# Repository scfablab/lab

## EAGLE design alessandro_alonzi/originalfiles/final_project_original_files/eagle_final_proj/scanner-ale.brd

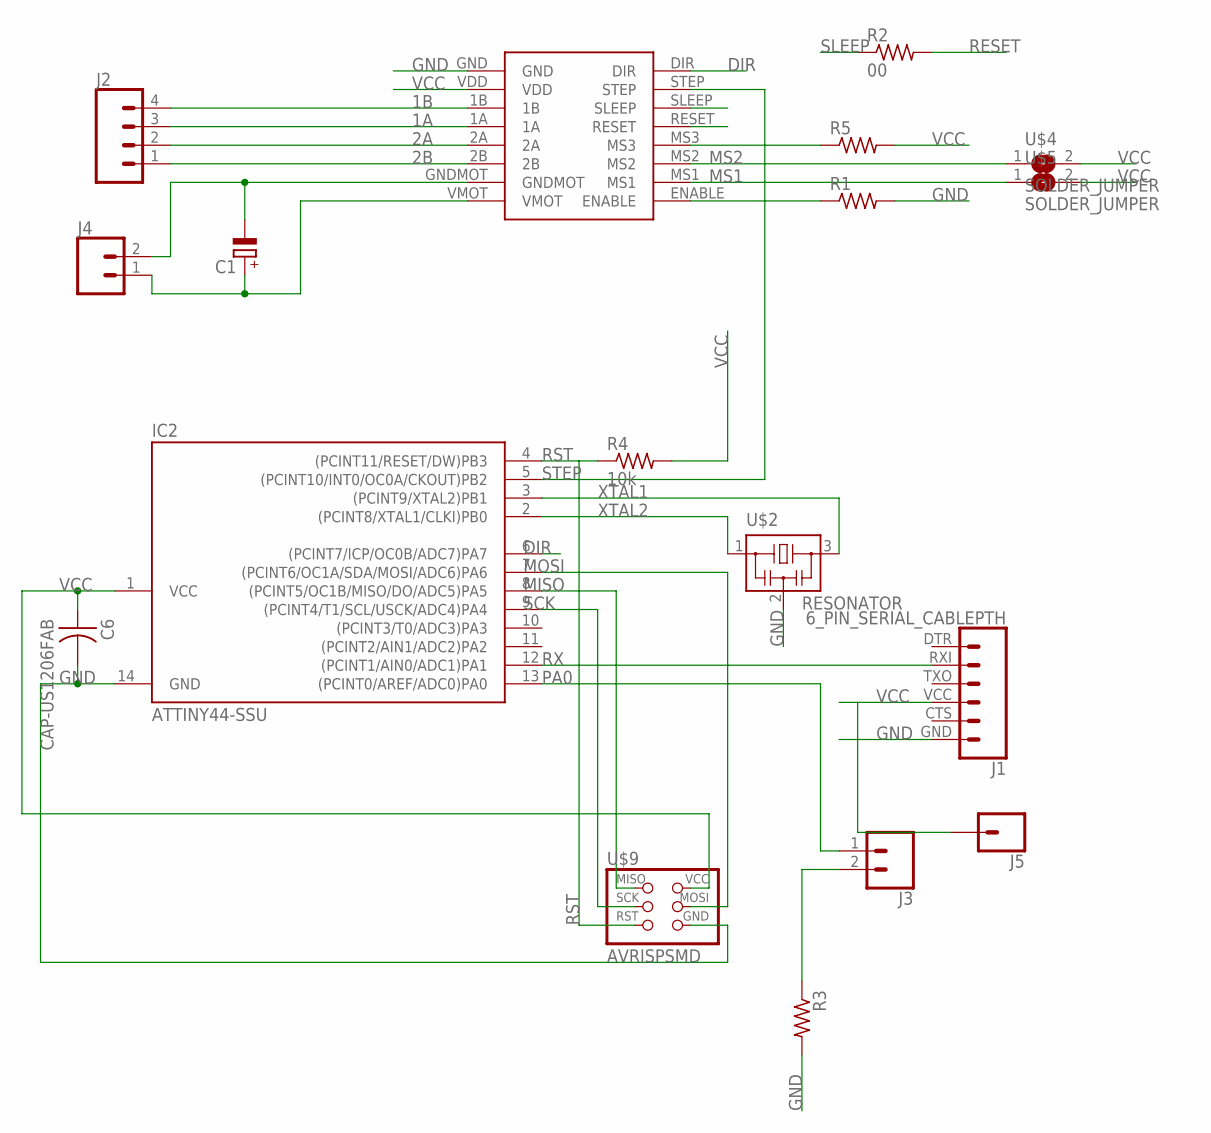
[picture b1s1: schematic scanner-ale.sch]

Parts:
C1: CPOL-EUE2,5-6E; E2,5-6E
C6: CAP-US1206FAB; C1206FAB
IC2: ATTINY44-SSU; SOIC14
J1: 6_PIN_SERIAL_CABLEPTH; FTDI_BASIC
J2: CONN_04; 1X04
J3, J4: CONN_02; 1X02
J5: CONN_01; 1X01
R1, R3, R5: RES-US1206FAB; R1206FAB
R2: 00; R1206FAB
R4: 10k; R1206FAB
U$1: POLOLUESTEPPERDRIVERDIL16MAT; DIL16
U$2: RESONATOR; EFOBM
U$4, U$5: SOLDER_JUMPER; SJFAB
U$9: AVRISPSMD; 2X03SMD

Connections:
1A: J2.3, U$1.1A
1B: J2.4, U$1.1B
2A: J2.2, U$1.2A
2B: J2.1, U$1.2B
DIR: IC2.6 ((PCINT7/ICP/OC0B/ADC7)PA7), U$1.DIR
GND: C6.2, IC2.14 (GND), J1.GND (6), R1.2, R3.2, U$1.GND, U$2.2, U$9.6 (GND)
MISO: IC2.8 ((PCINT5/OC1B/MISO/DO/ADC5)PA5), U$9.1 (MISO)
MOSI: IC2.7 ((PCINT6/OC1A/SDA/MOSI/ADC6)PA6), U$9.4 (MOSI)
MS1: U$1.MS1, U$5.1
MS2: U$1.MS2, U$4.1
unnamed: C1.-, J4.2, U$1.GNDMOT
unnamed: R1.1, U$1.ENABLE
unnamed: C1.+, J4.1, U$1.VMOT
unnamed: J3.2, R3.1
unnamed: R5.1, U$1.MS3
PA0: IC2.13 ((PCINT0/AREF/ADC0)PA0), J3.1
RESET: R2.2, U$1.RESET
RST: IC2.4 ((PCINT11/RESET/DW)PB3), R4.1, U$9.5 (RST)
RX: IC2.12 ((PCINT1/AIN0/ADC1)PA1), J1.RXI (2)
SCK: IC2.9 ((PCINT4/T1/SCL/USCK/ADC4)PA4), U$9.3 (SCK)
SLEEP: R2.1, U$1.SLEEP
STEP: IC2.5 ((PCINT10/INT0/OC0A/CKOUT)PB2), U$1.STEP
VCC: C6.1, IC2.1 (VCC), J1.VCC (4), J5.1, R4.2, R5.2, U$1.VDD, U$4.2, U$5.2, U$9.2 (VCC)
XTAL1: IC2.3 ((PCINT9/XTAL2)PB1), U$2.3
XTAL2: IC2.2 ((PCINT8/XTAL1/CLKI)PB0), U$2.1

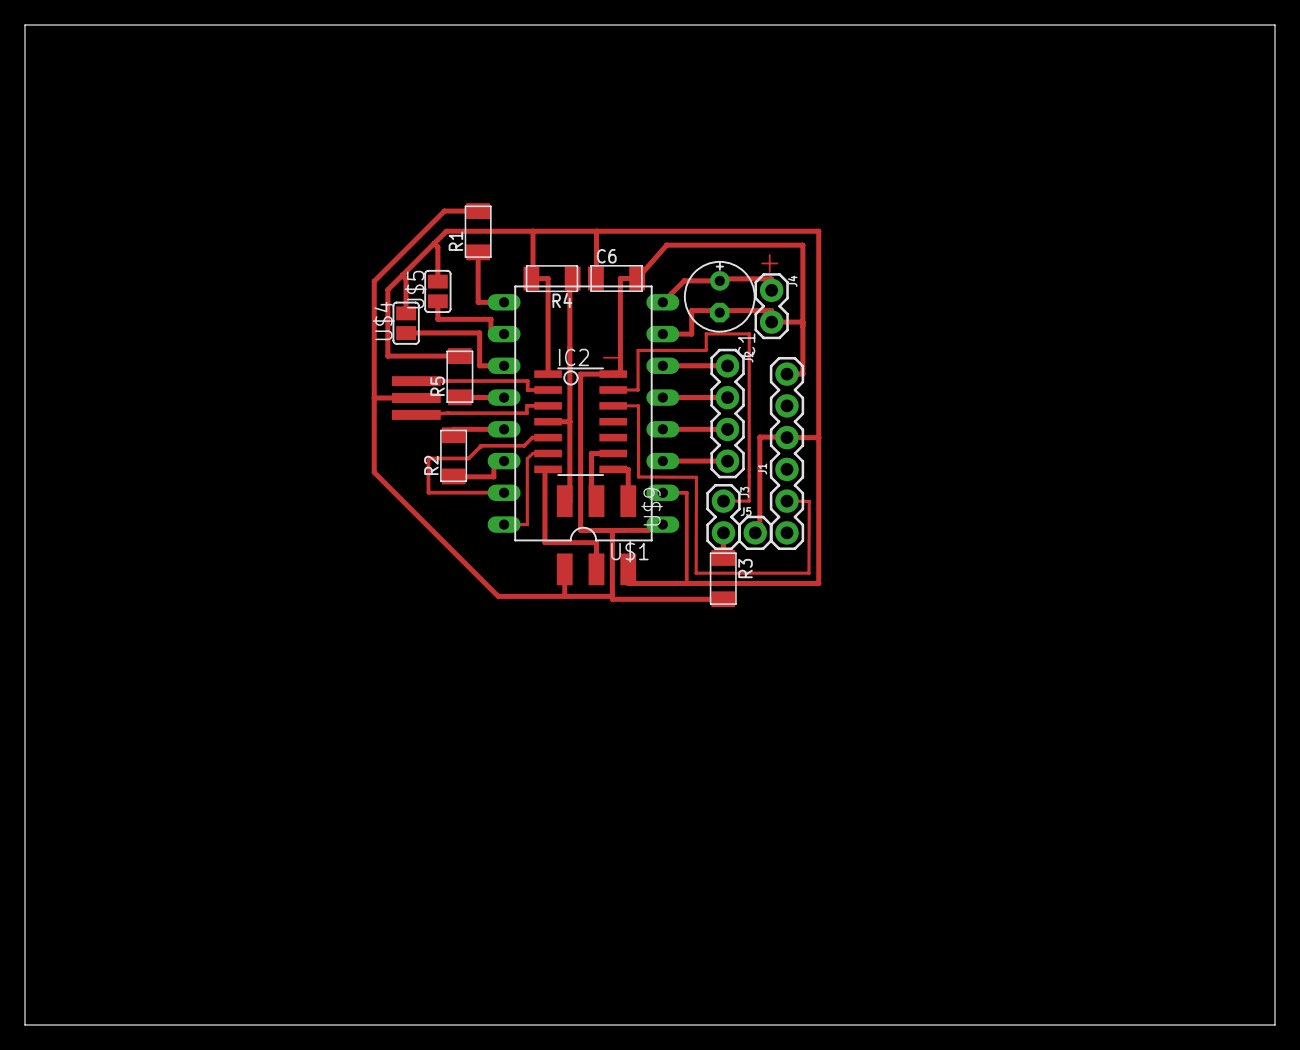
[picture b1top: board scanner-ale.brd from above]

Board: 2 copper layers, 100.0 x 80.0 mm, 18 parts (0 on the bottom side), 25 nets.

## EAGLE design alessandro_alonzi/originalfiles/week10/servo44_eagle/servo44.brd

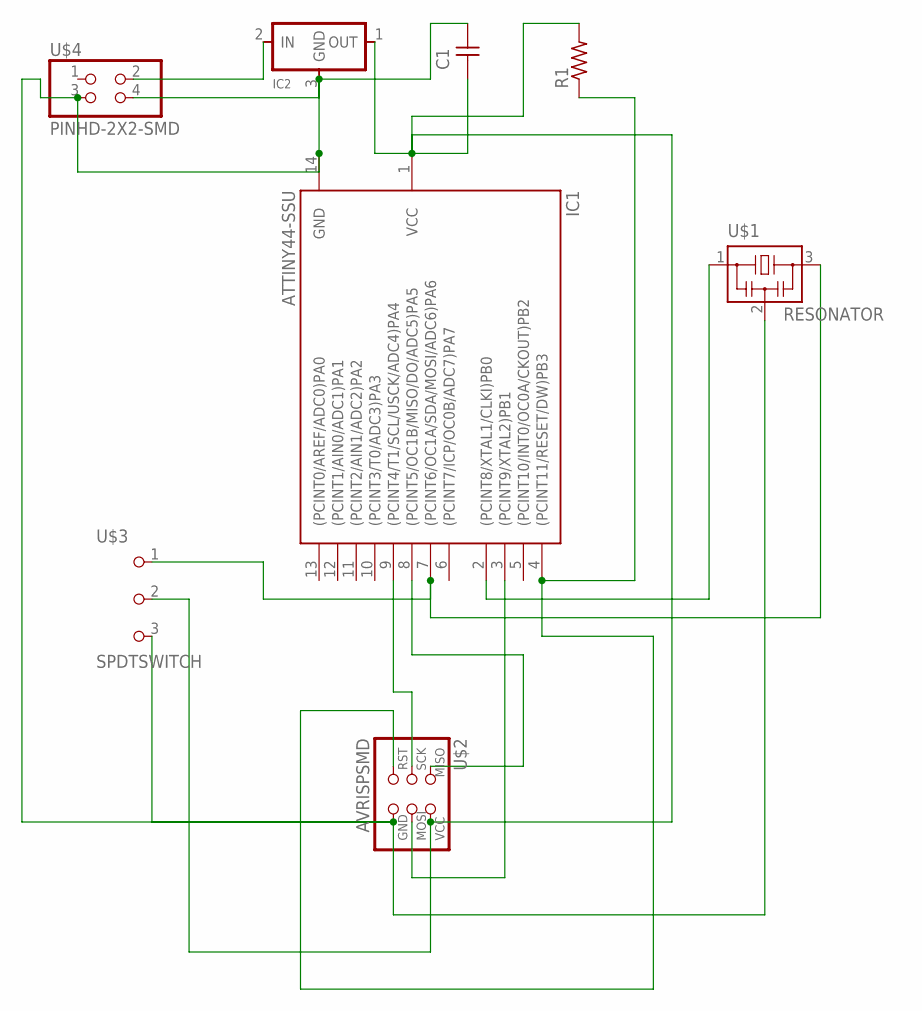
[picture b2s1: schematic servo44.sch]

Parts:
C1: CAP-UNPOLARIZEDFAB; C1206FAB
IC1: ATTINY44-SSU; SOIC14
IC2: REGULATORSOT23; SOT23
R1: RES-US1206FAB; R1206FAB
U$1: RESONATOR; EFOBM
U$2: AVRISPSMD; 2X03SMD
U$3: SPDTSWITCH
U$4: PINHD-2X2-SMD; 2X02SMD

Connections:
unnamed: IC1.8 ((PCINT5/OC1B/MISO/DO/ADC5)PA5), U$2.1 (MISO)
unnamed: IC1.9 ((PCINT4/T1/SCL/USCK/ADC4)PA4), U$2.3 (SCK)
unnamed: IC1.4 ((PCINT11/RESET/DW)PB3), R1.1, U$2.5 (RST)
unnamed: IC2.2 (IN), U$4.2
unnamed: IC1.7 ((PCINT6/OC1A/SDA/MOSI/ADC6)PA6), U$2.4 (MOSI), U$3.1
unnamed: C1.2, IC1.14 (GND), IC2.3 (GND), U$1.2, U$2.6 (GND), U$3.3, U$4.3, U$4.4
unnamed: IC1.2 ((PCINT8/XTAL1/CLKI)PB0), U$1.1
unnamed: IC1.3 ((PCINT9/XTAL2)PB1), U$1.3
unnamed: C1.1, IC1.1 (VCC), IC2.1 (OUT), R1.2, U$2.2 (VCC), U$3.2

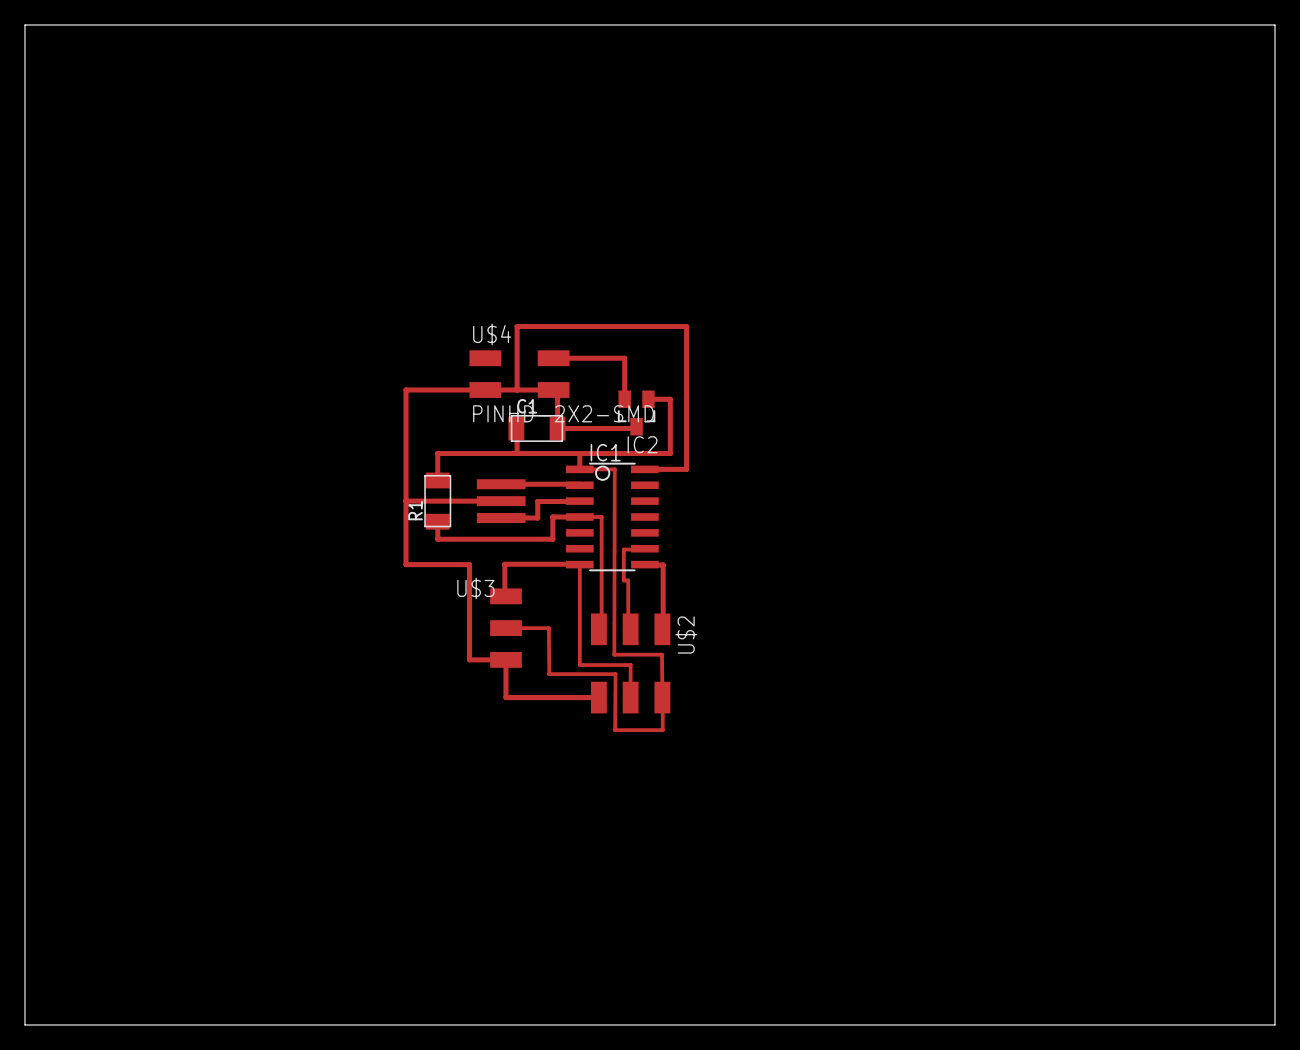
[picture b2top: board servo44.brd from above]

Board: 2 copper layers, 100.0 x 80.0 mm, 8 parts (0 on the bottom side), 9 nets.

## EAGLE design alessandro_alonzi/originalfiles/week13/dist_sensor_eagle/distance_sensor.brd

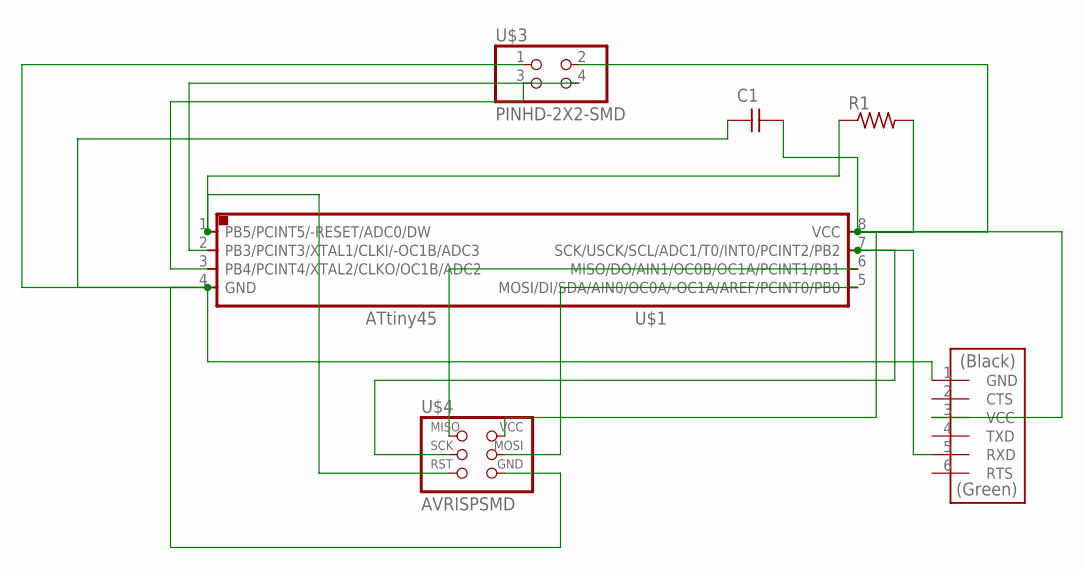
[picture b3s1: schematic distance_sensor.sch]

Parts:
C1: CAP-UNPOLARIZEDFAB; C1206FAB
R1: RES-US1206FAB; R1206FAB
U$1: ATTINY45SI; SOIC8
U$2: FTDI-SMD-HEADER; 1X06SMD
U$3: PINHD-2X2-SMD; 2X02SMD
U$4: AVRISPSMD; 2X03SMD

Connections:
unnamed: C1.1, U$1.4 (GND), U$2.1 (GND), U$3.1, U$4.6 (GND)
unnamed: C1.2, R1.2, U$1.8 (VCC), U$2.3 (VCC), U$3.2, U$4.2 (VCC)
unnamed: U$1.7 (SCK/USCK/SCL/ADC1/T0/INT0/PCINT2/PB2), U$2.5 (RXD), U$4.3 (SCK)
unnamed: U$1.3 (PB4/PCINT4/XTAL2/CLKO/OC1B/ADC2), U$3.3
unnamed: U$1.2 (PB3/PCINT3/XTAL1/CLKI/-OC1B/ADC3), U$3.4
unnamed: U$1.6 (MISO/DO/AIN1/OC0B/OC1A/PCINT1/PB1), U$4.1 (MISO)
unnamed: U$1.5 (MOSI/DI/SDA/AIN0/OC0A/-OC1A/AREF/PCINT0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), U$4.4 (MOSI)
unnamed: R1.1, U$1.1 (PB5/PCINT5/-RESET/ADC0/DW), U$4.5 (RST)

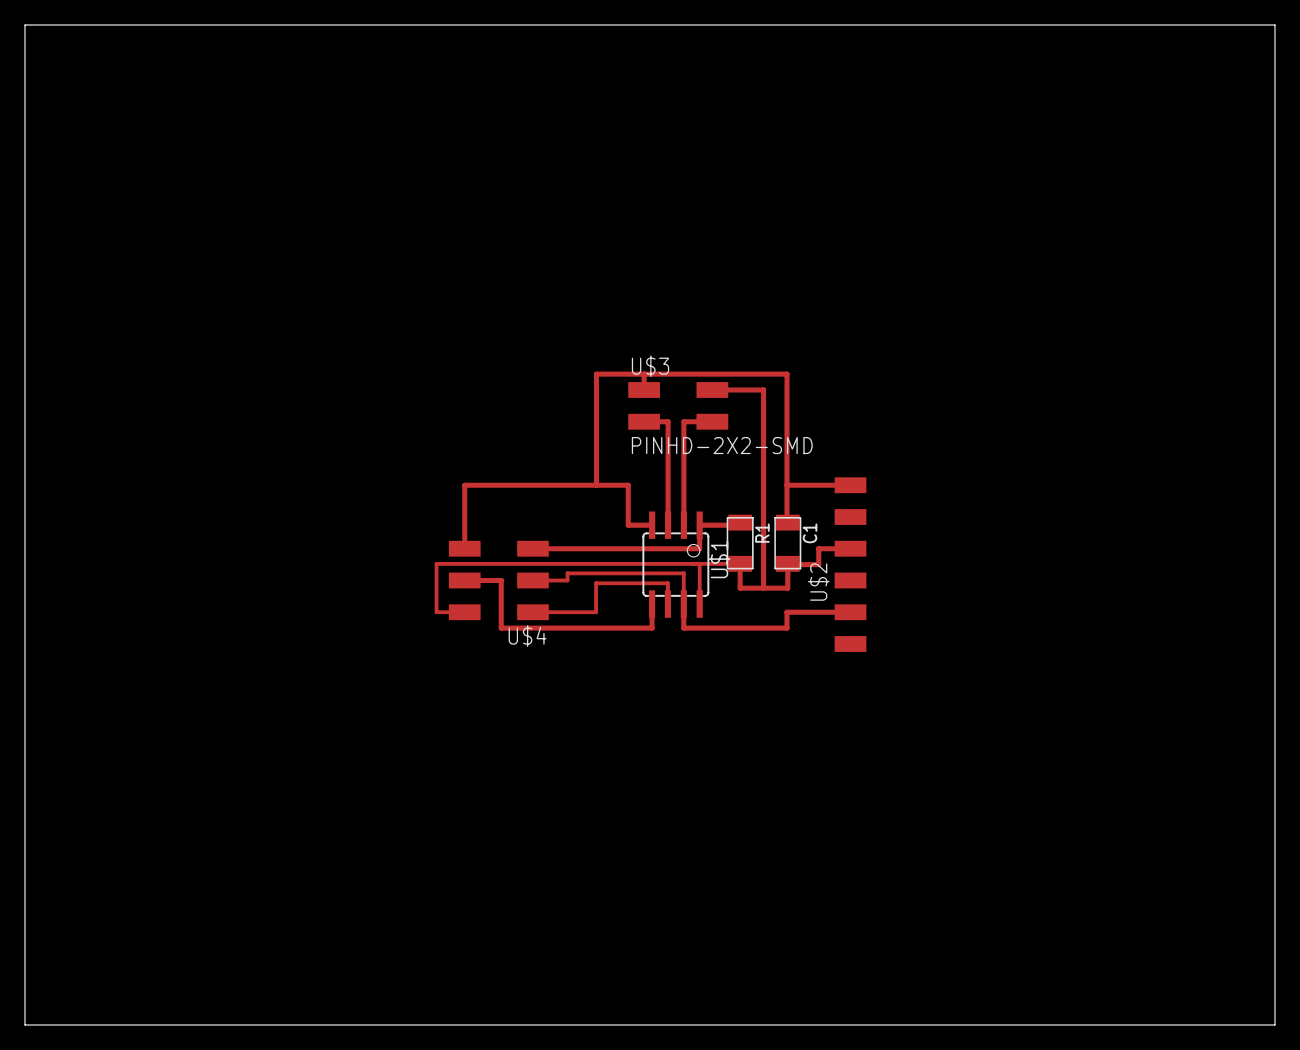
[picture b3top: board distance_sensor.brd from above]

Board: 2 copper layers, 100.0 x 80.0 mm, 6 parts (0 on the bottom side), 8 nets.

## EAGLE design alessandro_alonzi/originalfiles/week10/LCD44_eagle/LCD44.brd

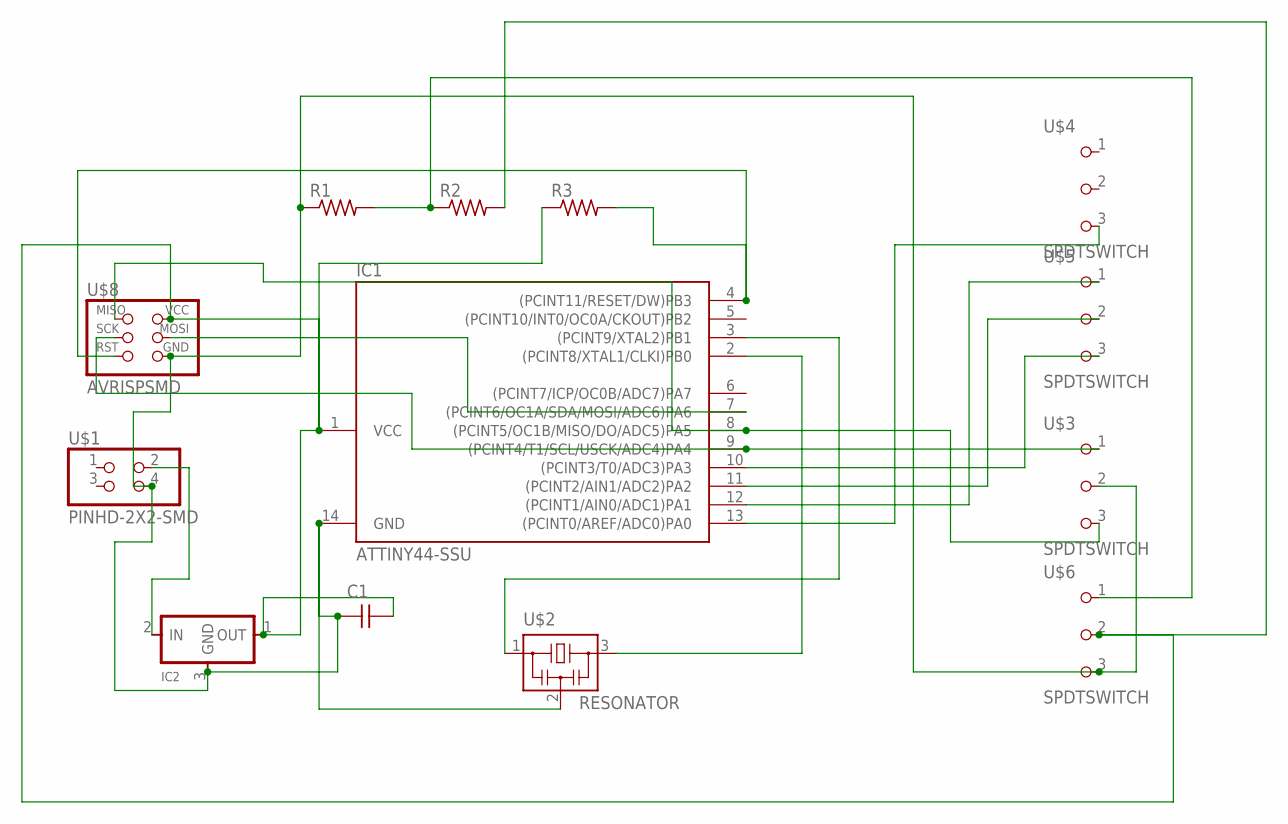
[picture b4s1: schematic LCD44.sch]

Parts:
C1: CAP-UNPOLARIZEDFAB; C1206FAB
IC1: ATTINY44-SSU; SOIC14
IC2: REGULATORSOT23; SOT23
R1, R2, R3: RES-US1206FAB; R1206FAB
U$1: PINHD-2X2-SMD; 2X02SMD
U$2: RESONATOR; EFOBM
U$3, U$4, U$5, U$6: SPDTSWITCH
U$8: AVRISPSMD; 2X03SMD

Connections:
unnamed: IC1.4 ((PCINT11/RESET/DW)PB3), R3.2, U$8.5 (RST)
unnamed: C1.2, IC1.1 (VCC), IC2.1 (OUT), R2.2, R3.1, U$6.2, U$8.2 (VCC)
unnamed: IC1.2 ((PCINT8/XTAL1/CLKI)PB0), U$2.3
unnamed: IC1.3 ((PCINT9/XTAL2)PB1), U$2.1
unnamed: IC1.7 ((PCINT6/OC1A/SDA/MOSI/ADC6)PA6), U$8.4 (MOSI)
unnamed: IC2.2 (IN), U$1.2
unnamed: C1.1, IC1.14 (GND), IC2.3 (GND), R1.1, U$1.4, U$2.2, U$3.2, U$6.3, U$8.6 (GND)
unnamed: IC1.9 ((PCINT4/T1/SCL/USCK/ADC4)PA4), U$3.1, U$8.3 (SCK)
unnamed: IC1.8 ((PCINT5/OC1B/MISO/DO/ADC5)PA5), U$3.3, U$8.1 (MISO)
unnamed: R1.2, R2.1, U$6.1
unnamed: IC1.10 ((PCINT3/T0/ADC3)PA3), U$5.3
unnamed: IC1.11 ((PCINT2/AIN1/ADC2)PA2), U$5.2
unnamed: IC1.12 ((PCINT1/AIN0/ADC1)PA1), U$5.1
unnamed: IC1.13 ((PCINT0/AREF/ADC0)PA0), U$4.3

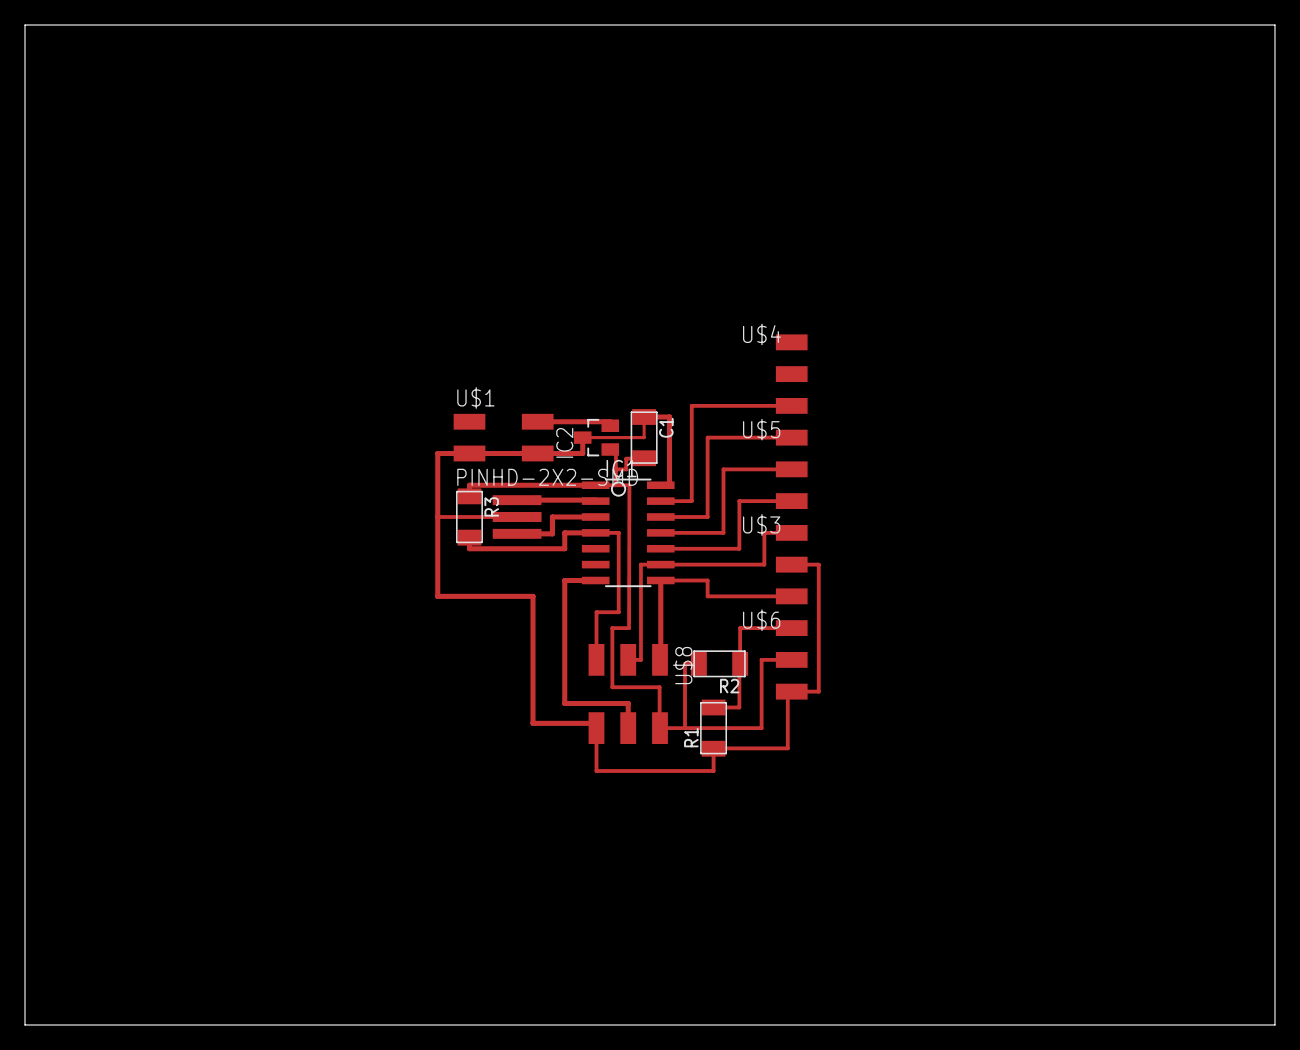
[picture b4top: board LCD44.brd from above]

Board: 2 copper layers, 100.0 x 80.0 mm, 13 parts (0 on the bottom side), 14 nets.

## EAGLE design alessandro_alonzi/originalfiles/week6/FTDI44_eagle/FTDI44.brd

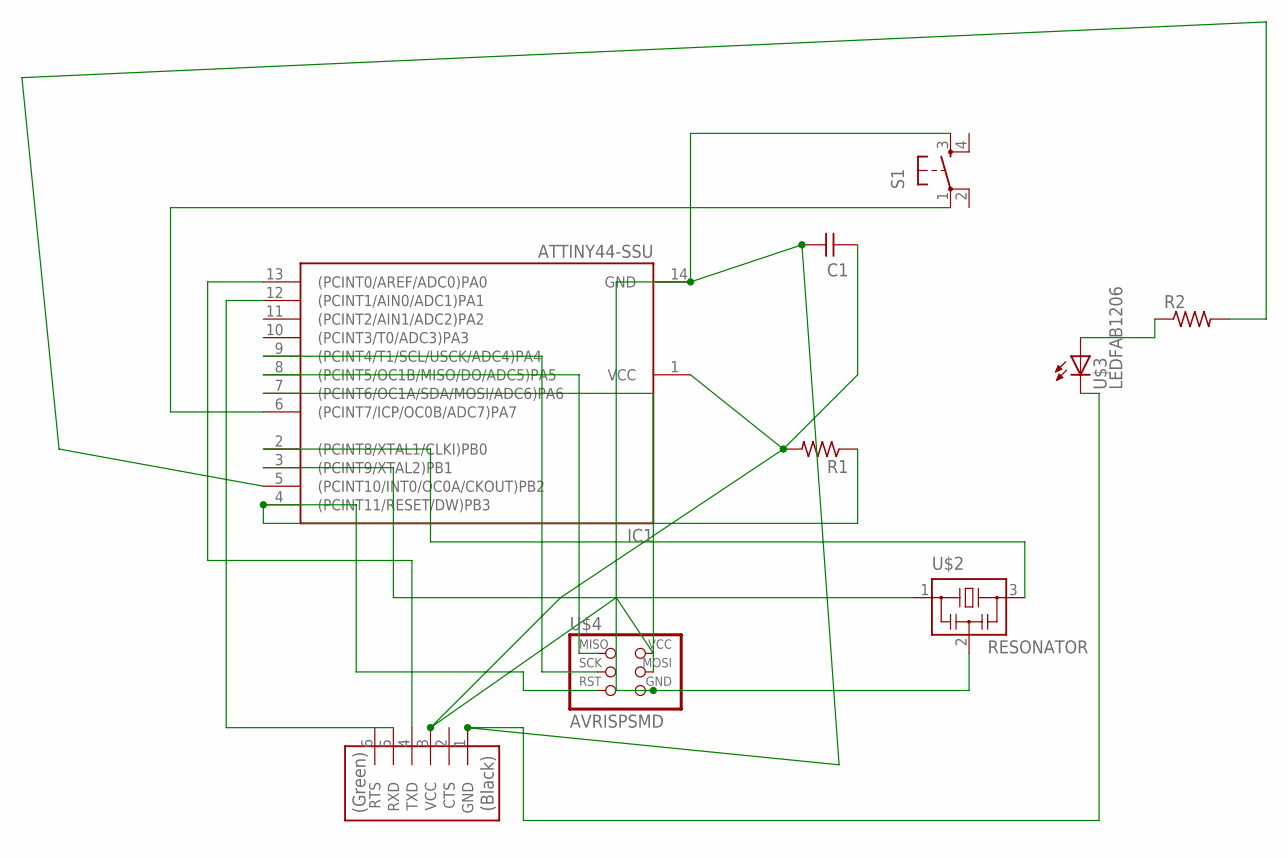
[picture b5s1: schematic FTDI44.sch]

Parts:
C1: CAP-UNPOLARIZEDFAB; C1206FAB
IC1: ATTINY44-SSU; SOIC14
R1, R2: RES-US1206FAB; R1206FAB
S1: 6MM_SWITCH6MM_SWITCH; 6MM_SWITCH
U$1: FTDI-SMD-HEADER; 1X06SMD
U$2: RESONATOR; EFOBM
U$3: LEDFAB1206; LED1206FAB
U$4: AVRISPSMD; 2X03SMD

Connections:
unnamed: IC1.12 ((PCINT1/AIN0/ADC1)PA1), U$1.5 (RXD)
unnamed: C1.1, IC1.1 (VCC), R1.2, U$1.3 (VCC), U$4.2 (VCC)
unnamed: IC1.4 ((PCINT11/RESET/DW)PB3), R1.1, U$4.5 (RST)
unnamed: IC1.3 ((PCINT9/XTAL2)PB1), U$2.1
unnamed: IC1.2 ((PCINT8/XTAL1/CLKI)PB0), U$2.3
unnamed: C1.2, IC1.14 (GND), S1.3 (S), U$1.1 (GND), U$2.2, U$3.2 (C), U$4.6 (GND)
unnamed: IC1.13 ((PCINT0/AREF/ADC0)PA0), U$1.4 (TXD)
unnamed: IC1.8 ((PCINT5/OC1B/MISO/DO/ADC5)PA5), U$4.1 (MISO)
unnamed: IC1.7 ((PCINT6/OC1A/SDA/MOSI/ADC6)PA6), U$4.4 (MOSI)
unnamed: IC1.9 ((PCINT4/T1/SCL/USCK/ADC4)PA4), U$4.3 (SCK)
unnamed: R2.1, U$3.1 (A)
unnamed: IC1.6 ((PCINT7/ICP/OC0B/ADC7)PA7), S1.1
unnamed: IC1.5 ((PCINT10/INT0/OC0A/CKOUT)PB2), R2.2

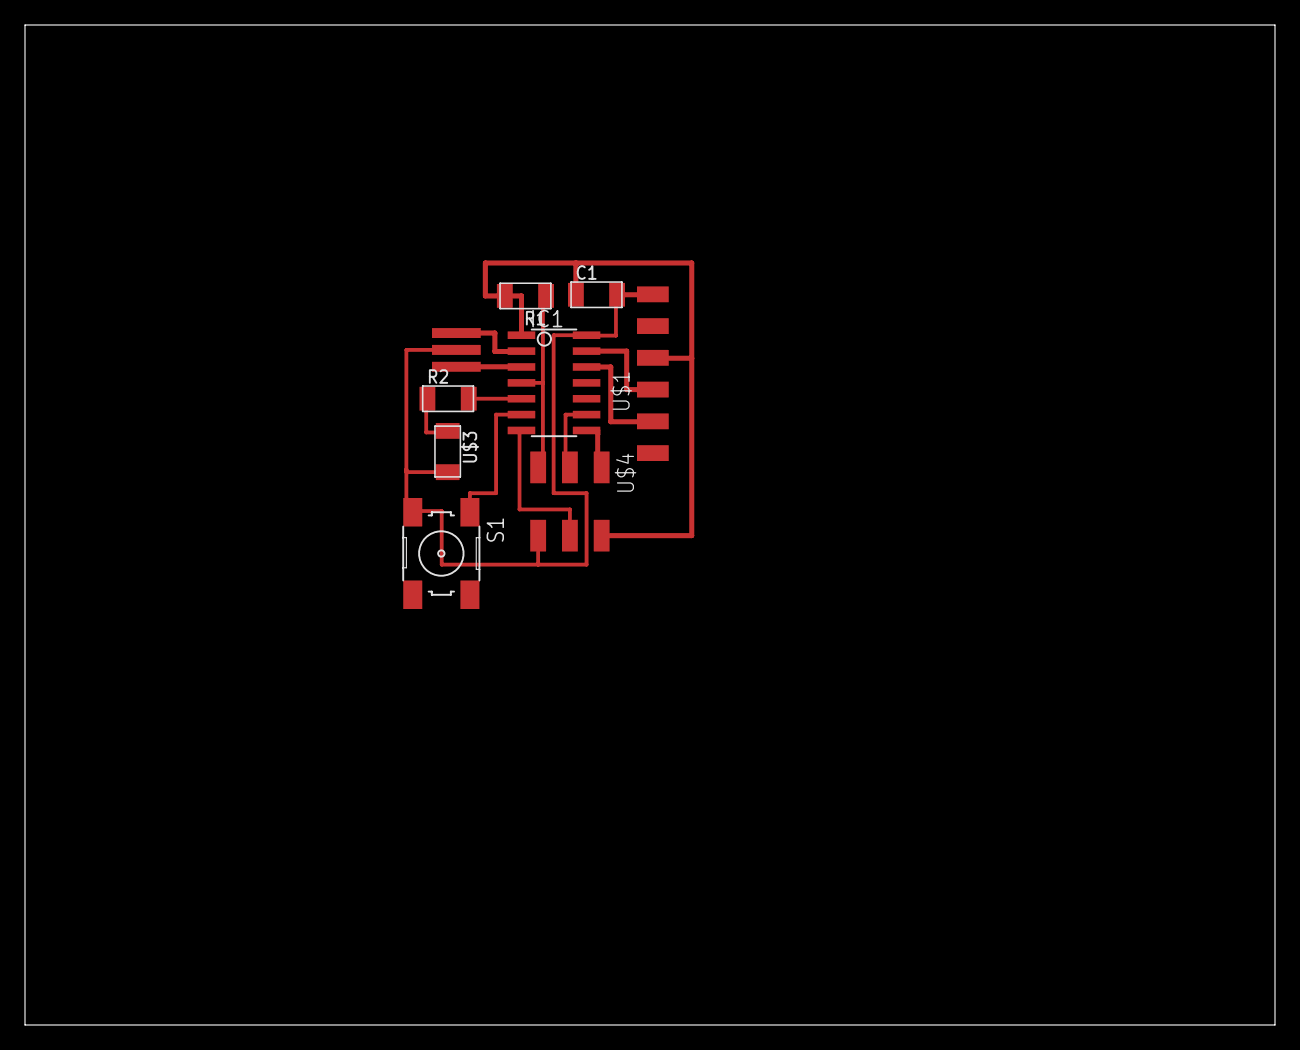
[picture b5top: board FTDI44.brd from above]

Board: 2 copper layers, 100.0 x 80.0 mm, 9 parts (0 on the bottom side), 13 nets.

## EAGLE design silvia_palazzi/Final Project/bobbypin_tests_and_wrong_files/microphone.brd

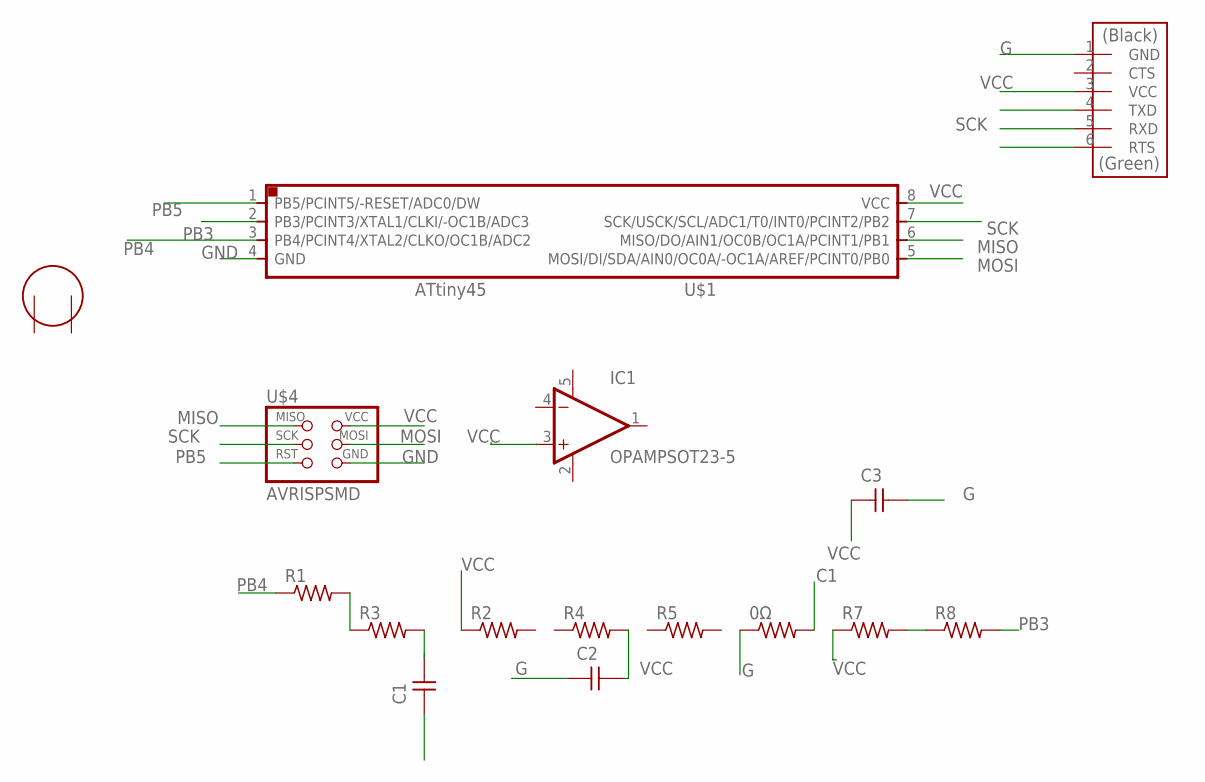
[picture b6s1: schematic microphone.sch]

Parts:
0Ω: RES-US1206FAB; R1206FAB
C1, C2, C3: CAP-UNPOLARIZEDFAB; C1206FAB
IC1: OPAMPSOT23-5; SOT23-5
R1, R2, R3, R4, R5, R7, R8: RES-US1206FAB; R1206FAB
U$1: ATTINY45SI; SOIC8
U$2: FTDI-SMD-HEADER; 1X06SMD
U$4: AVRISPSMD; 2X03SMD
U$5: ELECTRET; ELECTRET_2742PBJ-A

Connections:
C1: 0Ω.2
G: 0Ω.1, C2.1, C3.2, U$2.1 (GND)
GND: U$1.4 (GND), U$4.6 (GND)
MISO: U$1.6 (MISO/DO/AIN1/OC0B/OC1A/PCINT1/PB1), U$4.1 (MISO)
MOSI: U$1.5 (MOSI/DI/SDA/AIN0/OC0A/-OC1A/AREF/PCINT0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), U$4.4 (MOSI)
unnamed: R7.2, R8.1
unnamed: R1.2, R3.1
unnamed: C1.2, R3.2
PB3: R8.2, U$1.2 (PB3/PCINT3/XTAL1/CLKI/-OC1B/ADC3)
PB4: R1.1, U$1.3 (PB4/PCINT4/XTAL2/CLKO/OC1B/ADC2)
PB5: U$1.1 (PB5/PCINT5/-RESET/ADC0/DW), U$4.5 (RST)
SCK: U$1.7 (SCK/USCK/SCL/ADC1/T0/INT0/PCINT2/PB2), U$2.5 (RXD), U$4.3 (SCK)
V+: IC1.5 (V+)
V-: IC1.2 (V-)
VCC: C2.2, C3.1, R2.1, R4.2, R7.1, U$1.8 (VCC), U$2.3 (VCC), U$4.2 (VCC)

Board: 2 copper layers, 16 parts (0 on the bottom side), 12 nets, no tracks yet.

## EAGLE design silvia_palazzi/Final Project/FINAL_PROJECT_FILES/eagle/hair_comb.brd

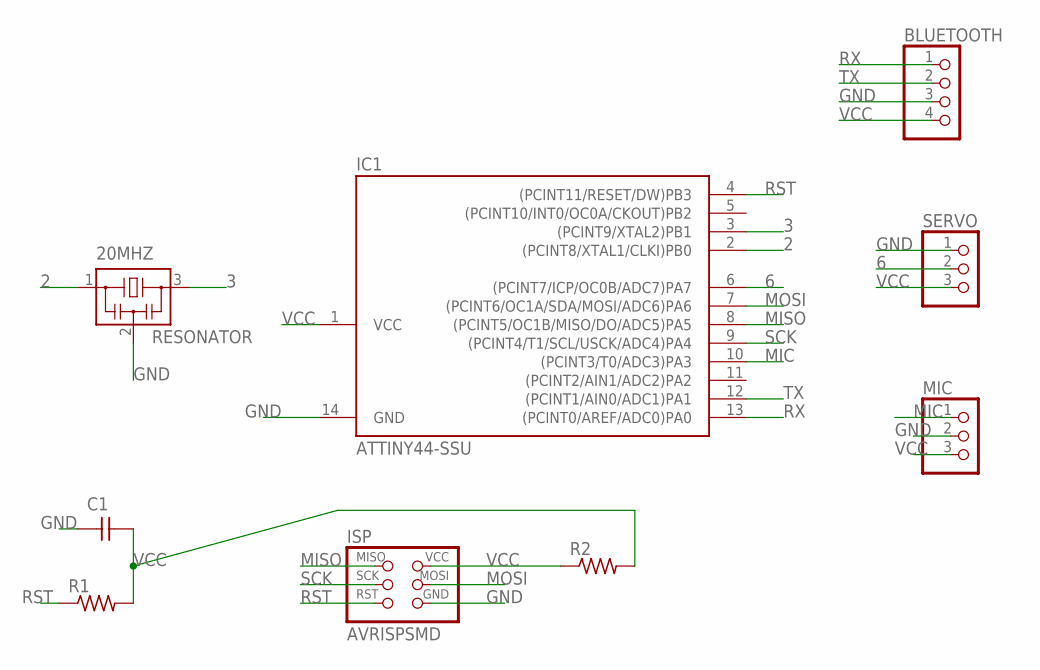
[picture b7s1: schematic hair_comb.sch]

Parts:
20MHZ: RESONATOR; EFOBM
BLUETOOTH: PINHD-1X4/90; 1X04/90
C1: CAP-UNPOLARIZEDFAB; C1206FAB
IC1: ATTINY44-SSU; SOIC14
ISP: AVRISPSMD; 2X03SMD
MIC: PINHD-1X3/90; 1X03/90
R1, R2: RES-US1206FAB; R1206FAB
SERVO: PINHD-1X3/90; 1X03/90

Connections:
2: 20MHZ.1, IC1.2 ((PCINT8/XTAL1/CLKI)PB0)
3: 20MHZ.3, IC1.3 ((PCINT9/XTAL2)PB1)
6: IC1.6 ((PCINT7/ICP/OC0B/ADC7)PA7), SERVO.2
GND: 20MHZ.2, BLUETOOTH.3, C1.1, IC1.14 (GND), ISP.6 (GND), MIC.2, SERVO.1
MIC: IC1.10 ((PCINT3/T0/ADC3)PA3), MIC.1
MISO: IC1.8 ((PCINT5/OC1B/MISO/DO/ADC5)PA5), ISP.1 (MISO)
MOSI: IC1.7 ((PCINT6/OC1A/SDA/MOSI/ADC6)PA6), ISP.4 (MOSI)
RST: IC1.4 ((PCINT11/RESET/DW)PB3), ISP.5 (RST), R1.1
RX: BLUETOOTH.1, IC1.13 ((PCINT0/AREF/ADC0)PA0)
SCK: IC1.9 ((PCINT4/T1/SCL/USCK/ADC4)PA4), ISP.3 (SCK)
TX: BLUETOOTH.2, IC1.12 ((PCINT1/AIN0/ADC1)PA1)
VCC: BLUETOOTH.4, C1.2, IC1.1 (VCC), ISP.2 (VCC), MIC.3, R1.2, R2.1, R2.2, SERVO.3

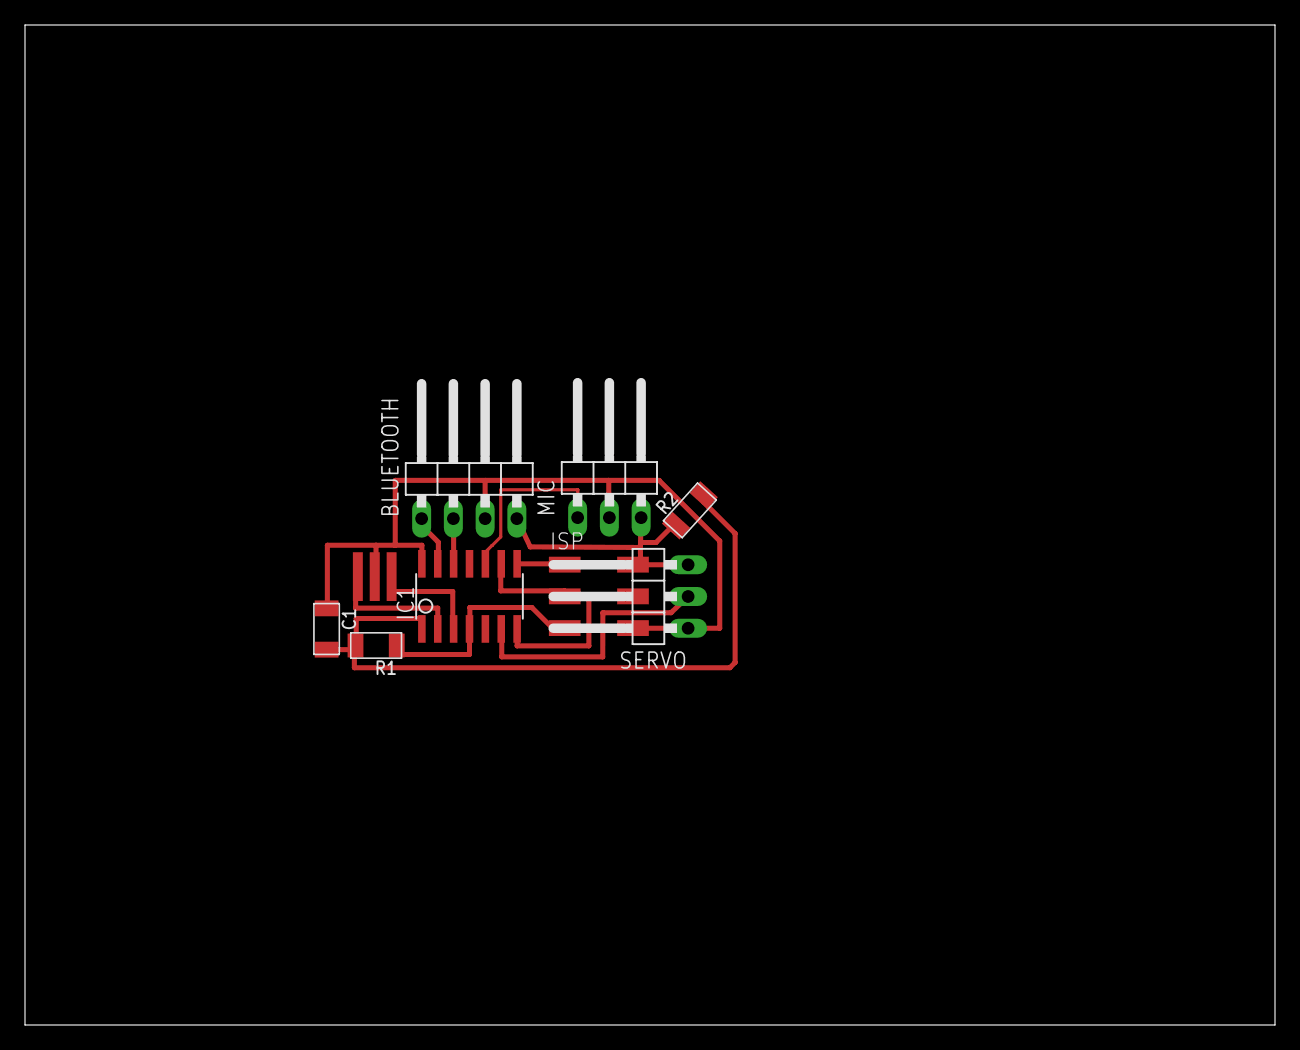
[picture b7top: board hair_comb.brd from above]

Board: 2 copper layers, 100.0 x 80.0 mm, 9 parts (0 on the bottom side), 12 nets.

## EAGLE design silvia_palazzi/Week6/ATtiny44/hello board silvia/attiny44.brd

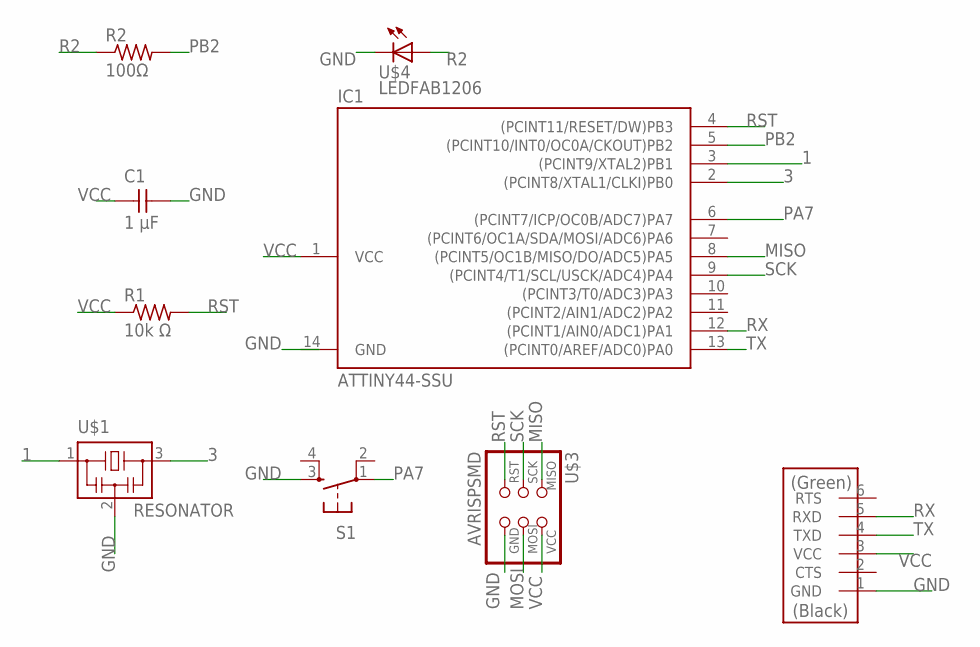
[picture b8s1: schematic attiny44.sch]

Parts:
C1: 1 µF; C1206FAB
IC1: ATTINY44-SSU; SOIC14
R1: 10k Ω; R1206FAB
R2: 100Ω; R1206FAB
S1: 6MM_SWITCH6MM_SWITCH; 6MM_SWITCH
U$1: RESONATOR; EFOBM
U$2: FTDI-SMD-HEADER; 1X06SMD
U$3: AVRISPSMD; 2X03SMD
U$4: LEDFAB1206; LED1206FAB

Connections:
1: IC1.3 ((PCINT9/XTAL2)PB1), U$1.1
3: IC1.2 ((PCINT8/XTAL1/CLKI)PB0), U$1.3
GND: C1.2, IC1.14 (GND), S1.3 (S), U$1.2, U$2.1 (GND), U$3.6 (GND), U$4.2 (C)
MISO: IC1.8 ((PCINT5/OC1B/MISO/DO/ADC5)PA5), U$3.1 (MISO)
MOSI: U$3.4 (MOSI)
PA7: IC1.6 ((PCINT7/ICP/OC0B/ADC7)PA7), S1.1
PB2: IC1.5 ((PCINT10/INT0/OC0A/CKOUT)PB2), R2.2
R2: R2.1, U$4.1 (A)
RST: IC1.4 ((PCINT11/RESET/DW)PB3), R1.2, U$3.5 (RST)
RX: IC1.12 ((PCINT1/AIN0/ADC1)PA1), U$2.5 (RXD)
SCK: IC1.9 ((PCINT4/T1/SCL/USCK/ADC4)PA4), U$3.3 (SCK)
TX: IC1.13 ((PCINT0/AREF/ADC0)PA0), U$2.4 (TXD)
VCC: C1.1, IC1.1 (VCC), R1.1, U$2.3 (VCC), U$3.2 (VCC)

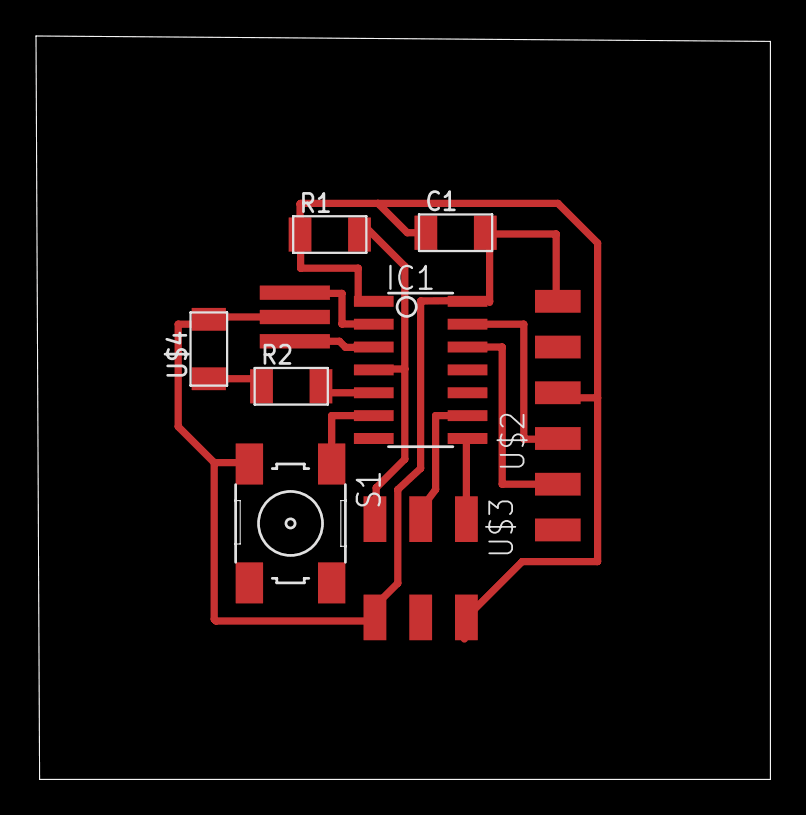
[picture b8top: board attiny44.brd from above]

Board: 2 copper layers, 40.8 x 41.3 mm, 9 parts (0 on the bottom side), 12 nets.

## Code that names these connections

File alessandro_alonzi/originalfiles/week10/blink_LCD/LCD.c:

#include <avr/io.h>
#include <util/delay.h>
#include <avr/pgmspace.h>

#define output(directions,pin) (directions |= pin) // set port direction for output
#define set(port,pin) (port |= pin) // set port pin
#define clear(port,pin) (port &= (~pin)) // clear port pin
#define pin_test(pins,pin) (pins & pin) // test for port pin
#define bit_test(byte,bit) (byte & (1 << bit)) // test for bit set

#define LCD_port PORTA
#define LCD_direction DDRA
#define DB7 (1 << PA0)
#define DB6 (1 << PA1)
#define DB5 (1 << PA2)
#define DB4 (1 << PA3)
#define E (1 << PA4)
#define RS (1 << PA5)

#define long_delay() _delay_ms(1000) // delay before redraw
#define lcd_delay() _delay_ms(10) // delay between commands
#define strobe_delay() _delay_us(1) // delay for strobe

//
// lcd_putchar
//    put character in lcdbyte
//
void lcd_putchar(char lcdbyte) {
   //
   // set RS for data
   // 
   set(LCD_port, RS);
   //
   // output high nibble
   //
   if bit_test(lcdbyte, 7)
      set(LCD_port, DB7);
   else
      clear(LCD_port, DB7);
   if bit_test(lcdbyte, 6)
      set(LCD_port, DB6);
   else
      clear(LCD_port, DB6);
   if bit_test(lcdbyte, 5)
      set(LCD_port, DB5);
   else
      clear(LCD_port, DB5);
   if bit_test(lcdbyte, 4)
      set(LCD_port, DB4);
   else
      clear(LCD_port, DB4);
   //
   // strobe E
   //
   strobe_delay();
   set(LCD_port, E);
   strobe_delay();
   clear(LCD_port, E);
   //
   // wait
   //
   lcd_delay();
   //
   // output low nibble
   //
   if bit_test(lcdbyte, 3)
      set(LCD_port, DB7);
   else
      clear(LCD_port, DB7);
   if bit_test(lcdbyte, 2)
      set(LCD_port, DB6);
   else
      clear(LCD_port, DB6);
   if bit_test(lcdbyte, 1)
      set(LCD_port, DB5);
   else
      clear(LCD_port, DB5);
   if bit_test(lcdbyte, 0)
      set(LCD_port, DB4);
   else
      clear(LCD_port, DB4);
   //
   // strobe E
   //
   strobe_delay();
   set(LCD_port, E);
   strobe_delay();
   clear(LCD_port, E);
   //
   // wait and return
   //
   lcd_delay();
   }
//
// lcd_putcmd
//    put command in lcdbyte
//
void lcd_putcmd(char lcdbyte) {
   //
   // clear RS for command
   // 
   clear(LCD_port, RS);
   //
   // output command bits
   //
   PORTA = lcdbyte;
   //
   // strobe E
   //
   strobe_delay();
   set(LCD_port, E);
   strobe_delay();
   clear(LCD_port, E);
   //
   // wait and return
   //
   lcd_delay();
   }
//
// lcd_putstring
//    put a null-terminated string in flash
//
void lcd_putstring(PGM_P message) {
   static uint8_t index;
   static char chr;
   index = 0;
   while (1) {
      chr = pgm_read_byte(&(message[index]));
      if (chr == 0)
         return;
      lcd_putchar(chr);
      ++index;
      }
   }
//
// lcd_init
//    initialize the LCD
//
void lcd_init() {
   //
   // power-up delay
   //
   lcd_delay();
   //
   // initialization sequence
   //
   lcd_putcmd(DB5+DB4);
   lcd_putcmd(DB5+DB4);
   lcd_putcmd(DB5+DB4);
   //
   // 4-bit interface
   //
   lcd_putcmd(DB5);
   //
   // two lines, 5x7 font
   //
   lcd_putcmd(DB5);
   lcd_putcmd(DB7);
   //
   // display on
   //
   lcd_putcmd(0);
   lcd_putcmd(DB7+DB6+DB5);
   //
   // entry mode
   //
   lcd_putcmd(0);
   lcd_putcmd(DB6+DB5);
   }

int main(void) {
   //
   // main
   //
   // set clock divider to /1
   //
   CLKPR = (1 << CLKPCE);
   CLKPR = (0 << CLKPS3) | (0 << CLKPS2) | (0 << CLKPS1) | (0 << CLKPS0);
   //
   // initialize LCD pins
   //
   clear(LCD_port, DB7);
   output(LCD_direction, DB7);
   clear(LCD_port, DB6);
   output(LCD_direction, DB6);
   clear(LCD_port, DB5);
   output(LCD_direction, DB5);
   clear(LCD_port, DB4);
   output(LCD_direction, DB4);
   clear(LCD_port, E);
   output(LCD_direction, E);
   clear(LCD_port, RS);
   output(LCD_direction, RS);
   //
   // initialize LCD
   //
   lcd_init();
   //
   // main loop
   //
   while (1) {
      // 
      // go to zero position
      //
      lcd_putcmd(0);
      lcd_putcmd(DB5);
      //
      // print first line from flash
      //
      static const char line1[] PROGMEM = "Hello to";
      lcd_putstring((PGM_P) line1);
      //
      // move to second line
      //
      lcd_putcmd(DB7+DB6);
      lcd_putcmd(0);
      //
      // print second line from flash
      //
      static const char line2[] PROGMEM = "the world";
      lcd_putstring((PGM_P) line2);
      //
      // pause
      //
      long_delay();
      //
      // clear display
      //
      lcd_putcmd(0);
      lcd_putcmd(DB4);
      }
   }

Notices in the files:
parts and their libraries:
01_SparkFun-Connectors: Licensing: Creative Commons ShareAlike 4.0 International - https://creativecommons.org/licenses/by-sa/4.0
